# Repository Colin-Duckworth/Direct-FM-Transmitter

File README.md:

# Direct FM Transmitter (80-115 MHz)

A component-level FM transmitter designed from scratch to demonstrate RF system design and PCB layout skills for applications in low-power, narrowband wireless communication.

## Project Overview

As of revision MK4, the system has been fully re-engineered to prioritize **manufacturability, affordability, and modular signal control**. The transmitter features:

- A **free-running VCO** directly modulated with an analog signal to produce wideband FM
- A **TI LMK61E2 programmable oscillator** used in place of a PLL synthesizer, simplifying the frequency control architecture while maintaining tunability and spectral stability
- A **mixer stage** that upconverts the modulated VCO signal using the oscillator output, enabling frequency offset generation
- A flexible **filtering stage**, configurable between a custom-designed 3–5 pole Butterworth bandpass filter and a wideband SAW filter depending on use case
- A **transformer balun** to convert 200 Ω differential signals to 50 Ω single-ended, improving impedance matching for the final power amplifier
- A two-stage **low-power RF amplifier chain** redesigned for improved linearity and thermal stability under higher output drive
- A **programmable digital potentiometer** in the VCO modulation path to dynamically adjust FM deviation and bandwidth
- An **on-board microcontroller interface** with tuning knob for real-time center frequency control
- Full **impedance matching** between all major blocks using standard-value passives and Pi attenuators to ensure operation within amplifier P1dB
- A layout optimized for **low-cost 4-layer PCB fabrication**, using only **common, non-exotic components** to minimize BOM cost and unique part count for low-volume assembly services like JLCPCB
- RF test points and SMA-tapped outputs for validation and debugging

The complete signal chain was simulated, measured, and iteratively refined based on real VNA and spectrum analyzer results, making this project both a learning platform and a functional RF transmitter.

## 🔁 Revision History

| Version | Date       | Summary of Changes |
|---------|------------|--------------------|
| **MK4** | 2025-07-14 | - Fully redesigned PCB to prioritize affordable manufacturability, minimizing unique component count and relying solely on standard, non-exotic passive components available from major low-cost assembly houses<br>- Replaced PLL synthesizer with the TI LMK61E2 programmable oscillator, simplifying frequency generation and reducing BOM complexity |
| **MK3** | 2025-07-03 | - Replaced previous fixed-frequency SAW filter with a wideband SAW filter to support flexible carrier generation<br>- Inserted a transformer balun after the SAW filter to convert 200 Ω differential output to 50 Ω single-ended, improving impedance matching and integration with the final PA<br>- Added low-noise preamplifiers before the passive mixer stage to improve upconversion SNR and mixer drive levels<br>- Modified the power amplifier chain for improved linearity and thermal performance under increased output drive<br>- Introduced a programmable digital potentiometer in the VCO modulation path to dynamically control modulation bandwidth, allowing application-specific FM deviation tuning<br>- Narrowed and finalized the carrier frequency range to 80–115 MHz for better compatibility with existing commercial and amateur FM-band antennas<br>- Integrated a microcontroller-interfaced tuning knob (potentiometer) to set center frequency, allowing real-time adjustment of carrier offset without reprogramming<br>- Added a level shifter IC between microcontroller I/O and the PLL synthesizer’s SPI interface to ensure proper logic-level compatibility |
| **MK2** | 2025-06-13 | - Replaced 50 MHz SAW filter with custom 3rd-order Butterworth filter to reduce insertion loss (~11 dB → <1 dB)<br>- Added second-stage amplifier to boost output power into 10–20 dBm range<br>- Inserted impedance-matched Pi attenuator before PA stages to ensure operation within P1dB<br>- Removed redundant RF tap after final amplifier (will probe SMA output directly if needed)<br>- Moved PLL Synth power supply from external microcontroller to on board power plane |
| **MK1** | 2025-05-02 | - Initial layout fabricated but not assembled<br>- SAW filter chain insertion loss (~15 dB) resulted in poor power budget<br>- No sufficient gain staging; final output estimated <1 mW<br>- Identified layout and topology flaws upon physical inspection<br>- Informed redesign of gain chain, filtering, and impedance matching in MK2 |

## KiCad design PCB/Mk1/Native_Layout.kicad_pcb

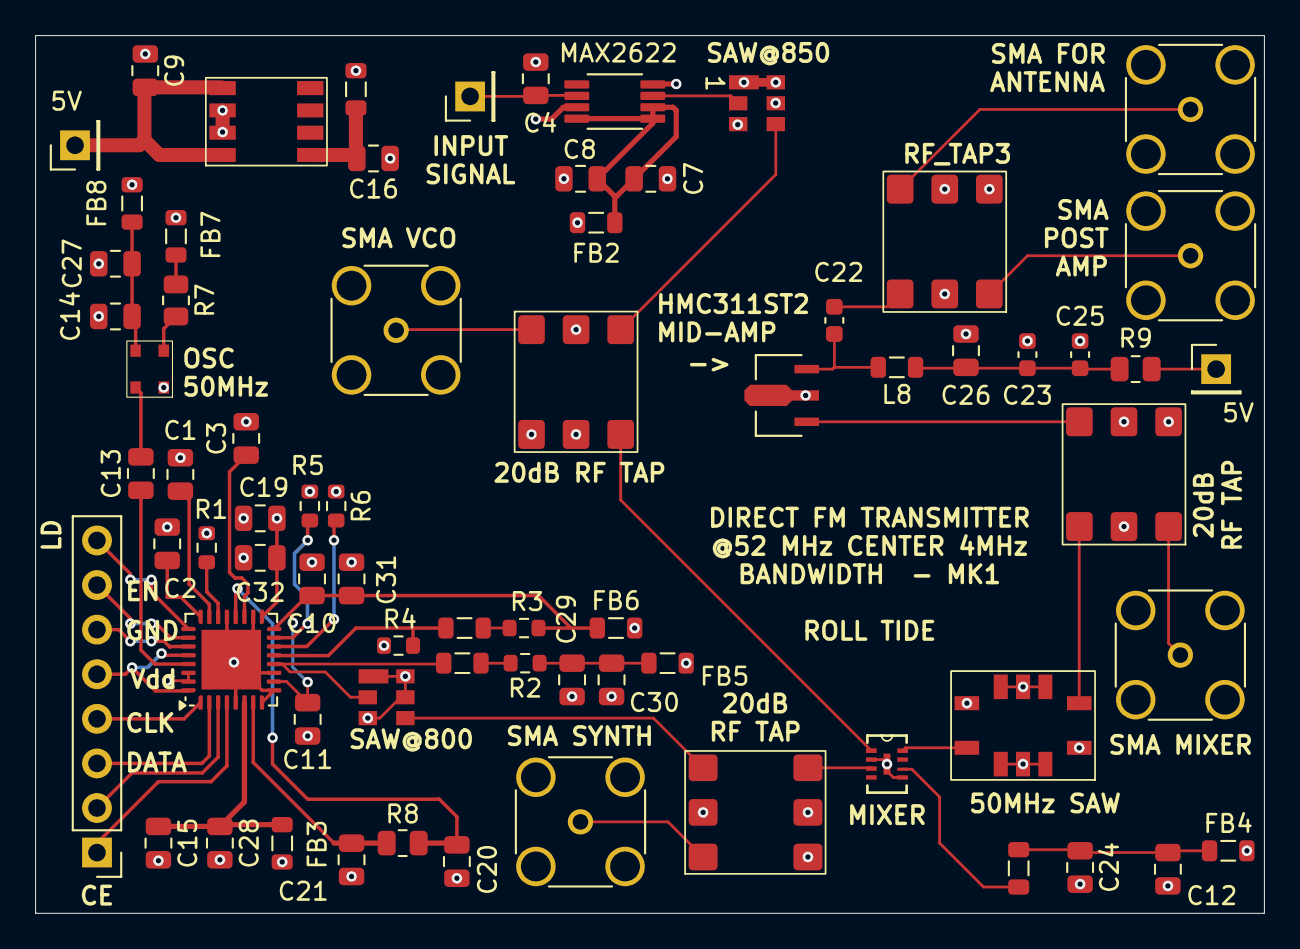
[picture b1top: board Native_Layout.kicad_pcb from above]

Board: 4 copper layers, 70.0 x 50.0 mm, 71 parts (0 on the bottom side), 53 nets.

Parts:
5V, 5V#2: 5V Supply; PinHeader_1x01_P2.54mm_Vertical
ADL1: CP-8-1
AP2112: SO-8 (AP2112)
C1, C2, C3, C4, C15, C29, C32: .1nF; C_0805_2012Metric
C7, C8, C9, C12, C14, C16, C20, C21: .1uF; C_0805_2012Metric
C10, C11: Decoup Cap; C_0805_2012Metric
C13: 4.7nF; C_0805_2012Metric
C19, C24, C27, C28, C30: 10uF; C_0805_2012Metric
C22: .01uF; C_0603_1608Metric
C23: 2.2u; C_0603_1608Metric
C25: 1000pF; C_0603_1608Metric
C26: 100pF; C_0805_2012Metric
C31: Bank Cap; C_0805_2012Metric
CE: Conn_01x08_Pin; PinHeader_1x08_P2.54mm_Vertical
FB2, FB3, FB4, FB5, FB6, FB7, FB8, FB9: RF choke; L_0805_2012Metric
HMC311ST2: SOT-89
J1: Conn_01x01_Pin; PinHeader_1x01_P2.54mm_Vertical
J2, J6, J7, J8, J9: Conn_Coaxial_Small; SMA_Amphenol_132134-14_Vertical
L8: 820nH; L_0805_2012Metric
MAX1: TQFN-32-1EP_5x5mm_P0.5mm_EP3.4x3.4mm
MAX2622: 8uMAX
R1, R2, R3, R4, R5, R6: 50ohm; R_0603_1608Metric
R7: 10k; R_0805_2012Metric
R8: 1000 ohm; R_0805_2012Metric
R9: 22 ohm; R_0805_2012Metric
RF_Choke2, RF_Choke4: 18nH; L_0805_2012Metric
RF_Choke3: 22nH; L_0805_2012Metric
RF_TAP1, RF_TAP2, RF_TAP3, RF_TAP4: RBDC-20
SAW@50: TAI-SAW Filter
SAW@800, SAW@850: Golledge SAW Footprint
U2: 4-Pin VSON (LMK6CE)

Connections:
GND1: ADL1.2 (GND2), ADL1.5 (GND1), ADL1.9 (Gnd), AP2112.6 (GND), AP2112.7 (GND), C1.2, C2.2, C3.2, C4.2, C7.1, C8.2, C9.1, C10.1, C11.2, C12.2, C14.1, C15.2, C16.1, C19.1, C20.1, C21.1, C23.1, C24.2, C25.1, C26.1, C27.2, C28.2, C29.2, C30.2, C31.1, C32.1, HMC311ST2.2 (GND), J2.2 (Ext), J6.2 (Ext), J7.2 (Ext), J8.2 (Ext), J9.2 (Ext), MAX1.5 (SW), MAX1.8 (GND_CP), MAX1.9 (GND_PLL), MAX1.11 (GND_RF), MAX1.18 (GND_VCO), MAX1.21 (GND_TUNE), MAX1.30 (MUX_OUT), MAX1.31 (GND_SD), MAX1.33 (GND), MAX2622.3 (GND), MAX2622.8 (GND), R1.2, R4.1, R5.1, R6.1, RF_TAP1.2 (GND), RF_TAP1.5 (GND), RF_TAP1.6 (GND), RF_TAP2.2 (GND), RF_TAP2.5 (GND), RF_TAP2.6 (GND), RF_TAP3.2 (GND), RF_TAP3.5 (GND), RF_TAP3.6 (GND), RF_TAP4.2 (GND), RF_TAP4.5 (GND), RF_TAP4.6 (GND), SAW@50.1 (GND), SAW@50.2 (GND), SAW@50.3 (GND), SAW@50.4 (GND), SAW@50.6 (GND), SAW@50.7 (GND), SAW@50.8 (GND), SAW@50.9 (GND), SAW@800.1 (GND), SAW@800.3 (GND), SAW@800.5 (GND), SAW@800.6 (GND), SAW@850.1 (GND), SAW@850.3 (GND), SAW@850.5 (GND), SAW@850.6 (GND), U2.2 (GND)
unnamed: ADL1.3 (LO_IN), RF_TAP1.4 (Output)
unnamed: ADL1.6 (VPOS), RF_Choke3.1
unnamed: 5V.1, AP2112.5 (En), AP2112.8 (Vin), C9.2
unnamed: AP2112.1 (Vout), C16.2, FB9.1
unnamed: C12.1, C24.1, FB4.1, RF_Choke3.2
unnamed: C23.2, C25.2, C26.2, L8.1, R9.2
unnamed: C29.1, C30.1, FB5.1, R2.1
unnamed: FB7.1, R7.1
unnamed: HMC311ST2.1 (In), RF_TAP2.4 (Output)
unnamed: C22.2, HMC311ST2.3 (OUT), L8.2
unnamed: C4.1, J1.1, MAX2622.2 (Tune)
unnamed: J2.1 (In), RF_TAP4.1 (Coupled)
unnamed: 5V#2.1, R9.1
unnamed: CE.1, MAX1.4 (CE)
unnamed: CE.2, MAX1.3 (LE)
unnamed: CE.3, MAX1.2 (Data)
unnamed: CE.4, MAX1.1 (CLK)
unnamed: CE.5, MAX1.28 (VCC_DIG), MAX1.32 (VDD_SD)
unnamed: CE.6, MAX1.27 (GND_DIG)
unnamed: CE.7, MAX1.26 (RFOUT_EN)
unnamed: CE.8, MAX1.25 (LD)
unnamed: J6.1 (In), RF_TAP1.1 (Coupled)
unnamed: J7.1 (In), RF_TAP2.1 (Coupled)
unnamed: J8.1 (In), RF_TAP3.1 (Coupled)
unnamed: J9.1 (In), RF_TAP3.4 (Output)
unnamed: C1.1, MAX1.23 (BIAS_FILT)
unnamed: C21.2, MAX1.7 (CP_OUT), R8.1
unnamed: C3.1, MAX1.19 (NOISE_FILT)
unnamed: C13.1, MAX1.29 (REF_IN)
unnamed: C2.1, MAX1.24 (REG)
unnamed: MAX1.13 (RFOUTA_N), R4.2, RF_Choke2.2
unnamed: MAX1.12 (RFOUTA_P), RF_Choke4.2, SAW@800.2 (Input)
unnamed: MAX1.15 (RFOUTB_N), R5.2
unnamed: MAX1.14 (RFOUTB_P), R6.2
unnamed: MAX1.22 (RSET), R1.1
unnamed: C20.2, MAX1.20 (TUNE), R8.2
unnamed: C15.1, C28.1, FB3.1, MAX1.6 (VCC_CP)
unnamed: C10.2, C11.1, C31.2, FB6.1, MAX1.10 (VCC_PLL), MAX1.16 (VCC_RF), R3.1
unnamed: C7.2, C8.1, FB2.2, MAX2622.4 (-SHDN), MAX2622.5 (Vcc), MAX2622.6 (Vcc)
unnamed: MAX2622.7 (Out), SAW@850.2 (Input)
unnamed: R2.2, RF_Choke4.1
unnamed: R3.2, RF_Choke2.1
unnamed: RF_TAP1.3 (Input), SAW@800.4 (Output)
unnamed: RF_TAP2.3 (Input), SAW@50.5 (Output)
unnamed: C22.1, RF_TAP3.3 (Input)
unnamed: RF_TAP4.3 (Input), SAW@850.4 (Output)
unnamed: ADL1.1 (RF/IF), RF_TAP4.4 (Output)
unnamed: ADL1.8 (RF/IF), SAW@50.10 (Input)
unnamed: R7.2, U2.1 (OE)
unnamed: C13.2, U2.3 (Out)
unnamed: C14.2, C27.1, FB8.2, U2.4 (Vdd)
VS: C19.2, C32.2, FB2.1, FB3.2, FB4.2, FB5.2, FB6.2, FB7.2, FB8.1, FB9.2, MAX1.17 (VCC_VCO)

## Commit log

2025-06-15 Rename FM_transmitter.pdf to Scematics/Mk1/FM_transmitter.pdf
2025-06-15 Rename FM_BUILD_MK1.zip to PCB/Mk1/FM_BUILD_MK1.zip
2025-06-15 Rename FM_transmitter.pdf to FM_transmitter.pdf
2025-06-15 Rename Screenshot 2025-06-15 162407.png to PCB.png
2025-06-19 Rename FM transmitter block diagram Mk2.pdf to Block-Diagram/MK2.pdf
2025-06-19 Rename MK2.pdf to MK2-Block-Diagram.pdf
2025-06-19 Rename FM transmitter block diagram Mk1.pdf to MK1-Block-Diagram.pdf
2025-06-20 Rename FM transmitter block diagram Mk2.pdf to Mk2-Block-Diagram.pdf
2025-07-16 Rename Schematics/GERBER-FM_transmitter.zip to PCB/Mk3/GERBER-FM_transmitter.zip
2025-07-16 Rename PCB/FM_PCB_MK2.zip to PCB/Mk2/FM_PCB_MK2.zip
2025-07-16 Rename PCB/GERBER-FM_transmitter.zip to PCB/Mk4/GERBER-FM_transmitter.zip
2025-07-16 Rename Screenshot 2025-07-15 203506.png to Mk4 PCB Png
2025-07-16 Rename Schematics/Screenshot 2025-07-15 203802.png to Schematics/Mk4/Screenshot 2025-07-15 203802.png
2025-07-16 Rename Screenshot 2025-07-15 203802.png to Mk4 Schematic.png
2025-07-16 Rename Mk4 PCB Png to Mk4 PCB Png.png
2025-07-16 Rename PCB/GERBER-FM_transmitter.zip to PCB/Mk3/PCB Mk3.zip
